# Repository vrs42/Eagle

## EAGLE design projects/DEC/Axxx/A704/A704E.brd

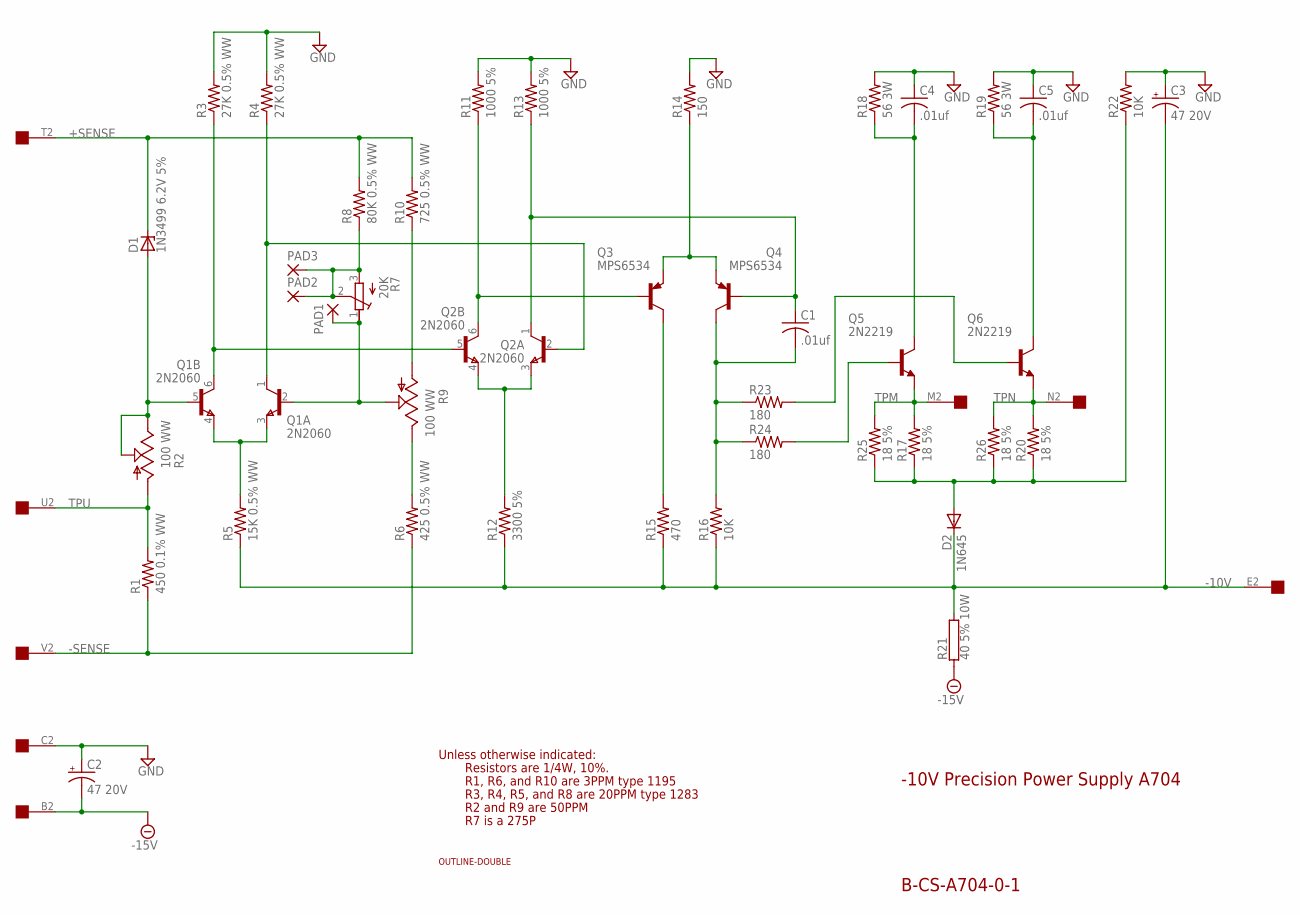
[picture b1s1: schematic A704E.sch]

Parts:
C1, C4, C5: .01uf; C050-025X075
C2, C3: 47 20V; E22-6
D1: 1N3499 6.2V 5%; DO35Z10
D2: 1N645; DO35-10
PAD1, PAD2, PAD3: 2,54/1,0
Q1, Q2: 2N2060; TO78
Q3, Q4: MPS6534; TO39
Q5, Q6: 2N2219; TO39
R1: 450 0.1% WW; P0817/22
R2, R9: 100 WW; S75P
R3, R4: 27K 0.5% WW; 0411/15
R5: 15K 0.5% WW; 0411/15
R6: 425 0.5% WW; P0817/22
R7: 20K; 3006Y
R8: 80K 0.5% WW; 0411/15
R10: 725 0.5% WW; P0817/22
R11, R13: 1000 5%; 0207/10
R12: 3300 5%; 0207/10
R14: 150; 0207/10
R15: 470; 0207/10
R16, R22: 10K; 0207/10
R17, R20, R25, R26: 18 5%; 0207/10
R18, R19: 56 3W; 0411/15
R21: 40 5% 10W; KH216-8
R23, R24: 180; 0207/10
U$2: OUTLINE-DOUBLE; DOUBLE
U$3: EDGE-1; EDGE-CON1

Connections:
+SENSE: D1.C, R8.2, R10.2, U$3.T2
-10V: C3.-, D2.C, R5.1, R12.1, R15.1, R16.1, R21.2, U$3.E2
-15V: C2.-, R21.1, U$3.B2
-SENSE: R1.1, R6.1, U$3.V2
GND: C2.+, C3.+, C4.1, C5.1, R3.2, R4.2, R11.2, R13.2, R14.2, R18.2, R19.2, R22.2, U$3.C2
unnamed: Q1.3 (E), Q1.4 (E), R5.2
unnamed: Q1.1 (C), Q2.2 (B), R4.1
unnamed: Q1.6 (C), Q2.5 (B), R3.1
unnamed: D1.A, Q1.5 (B), R2.E, R2.S
unnamed: R6.2, R9.E
unnamed: Q2.3 (E), Q2.4 (E), R12.2
unnamed: Q2.6 (C), Q3.2 (B), R11.1
unnamed: PAD1.1, Q1.2 (B), R7.1 (A), R9.S
unnamed: C1.1, Q2.1 (C), Q4.2 (B), R13.1
unnamed: Q3.3 (C), R15.2
unnamed: C1.2, Q4.3 (C), R16.2, R23.1, R24.1
unnamed: PAD2.1, PAD3.1, R7.2 (S), R7.3 (E), R8.1
unnamed: D2.A, R17.1, R20.1, R22.1, R25.1, R26.1
unnamed: Q3.1 (E), Q4.1 (E), R14.1
unnamed: Q5.2 (B), R24.2
unnamed: Q6.2 (B), R23.2
unnamed: C4.2, Q5.3 (C), R18.1
unnamed: C5.2, Q6.3 (C), R19.1
unnamed: R9.A, R10.1
TPM: Q5.1 (E), R17.2, R25.2, U$3.M2
TPN: Q6.1 (E), R20.2, R26.2, U$3.N2
TPU: R1.2, R2.A, U$3.U2

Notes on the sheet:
-10V Precision Power Supply A704
B-CS-A704-0-1
Unless otherwise indicated:
Resistors are 1/4W, 10%.
R7 is a 275P
R3, R4, R5, and R8 are 20PPM type 1283
R1, R6, and R10 are 3PPM type 1195
R2 and R9 are 50PPM

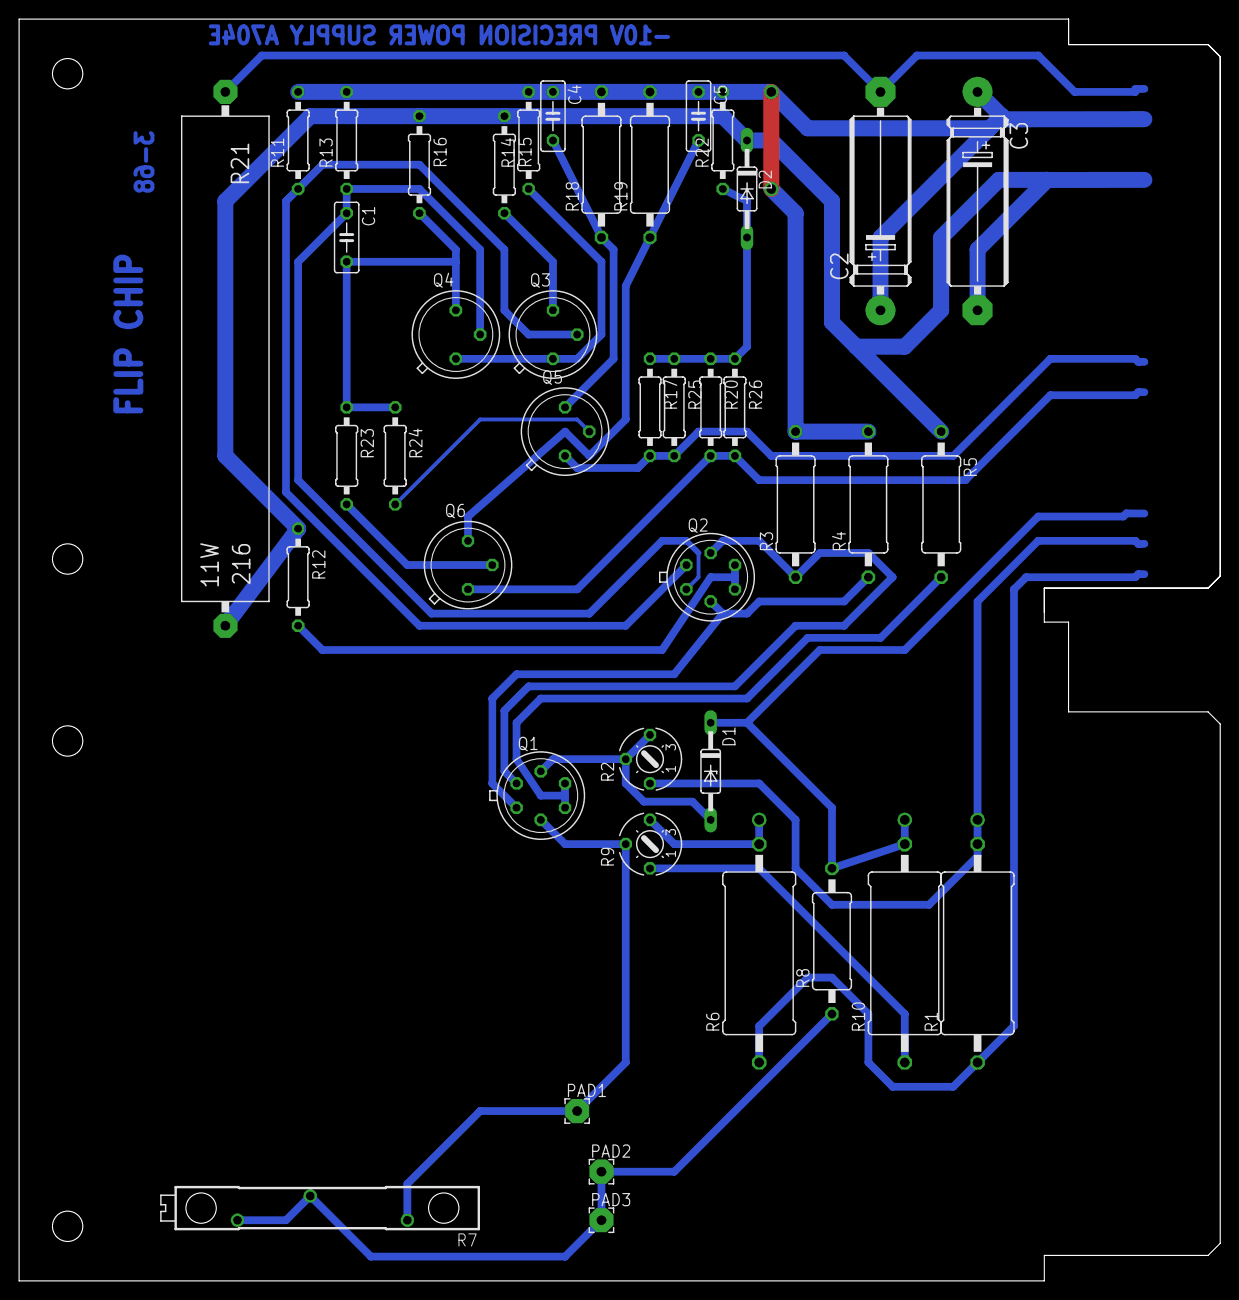
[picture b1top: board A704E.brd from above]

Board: 2 copper layers, 125.7 x 132.1 mm, 44 parts (0 on the bottom side), 27 nets.

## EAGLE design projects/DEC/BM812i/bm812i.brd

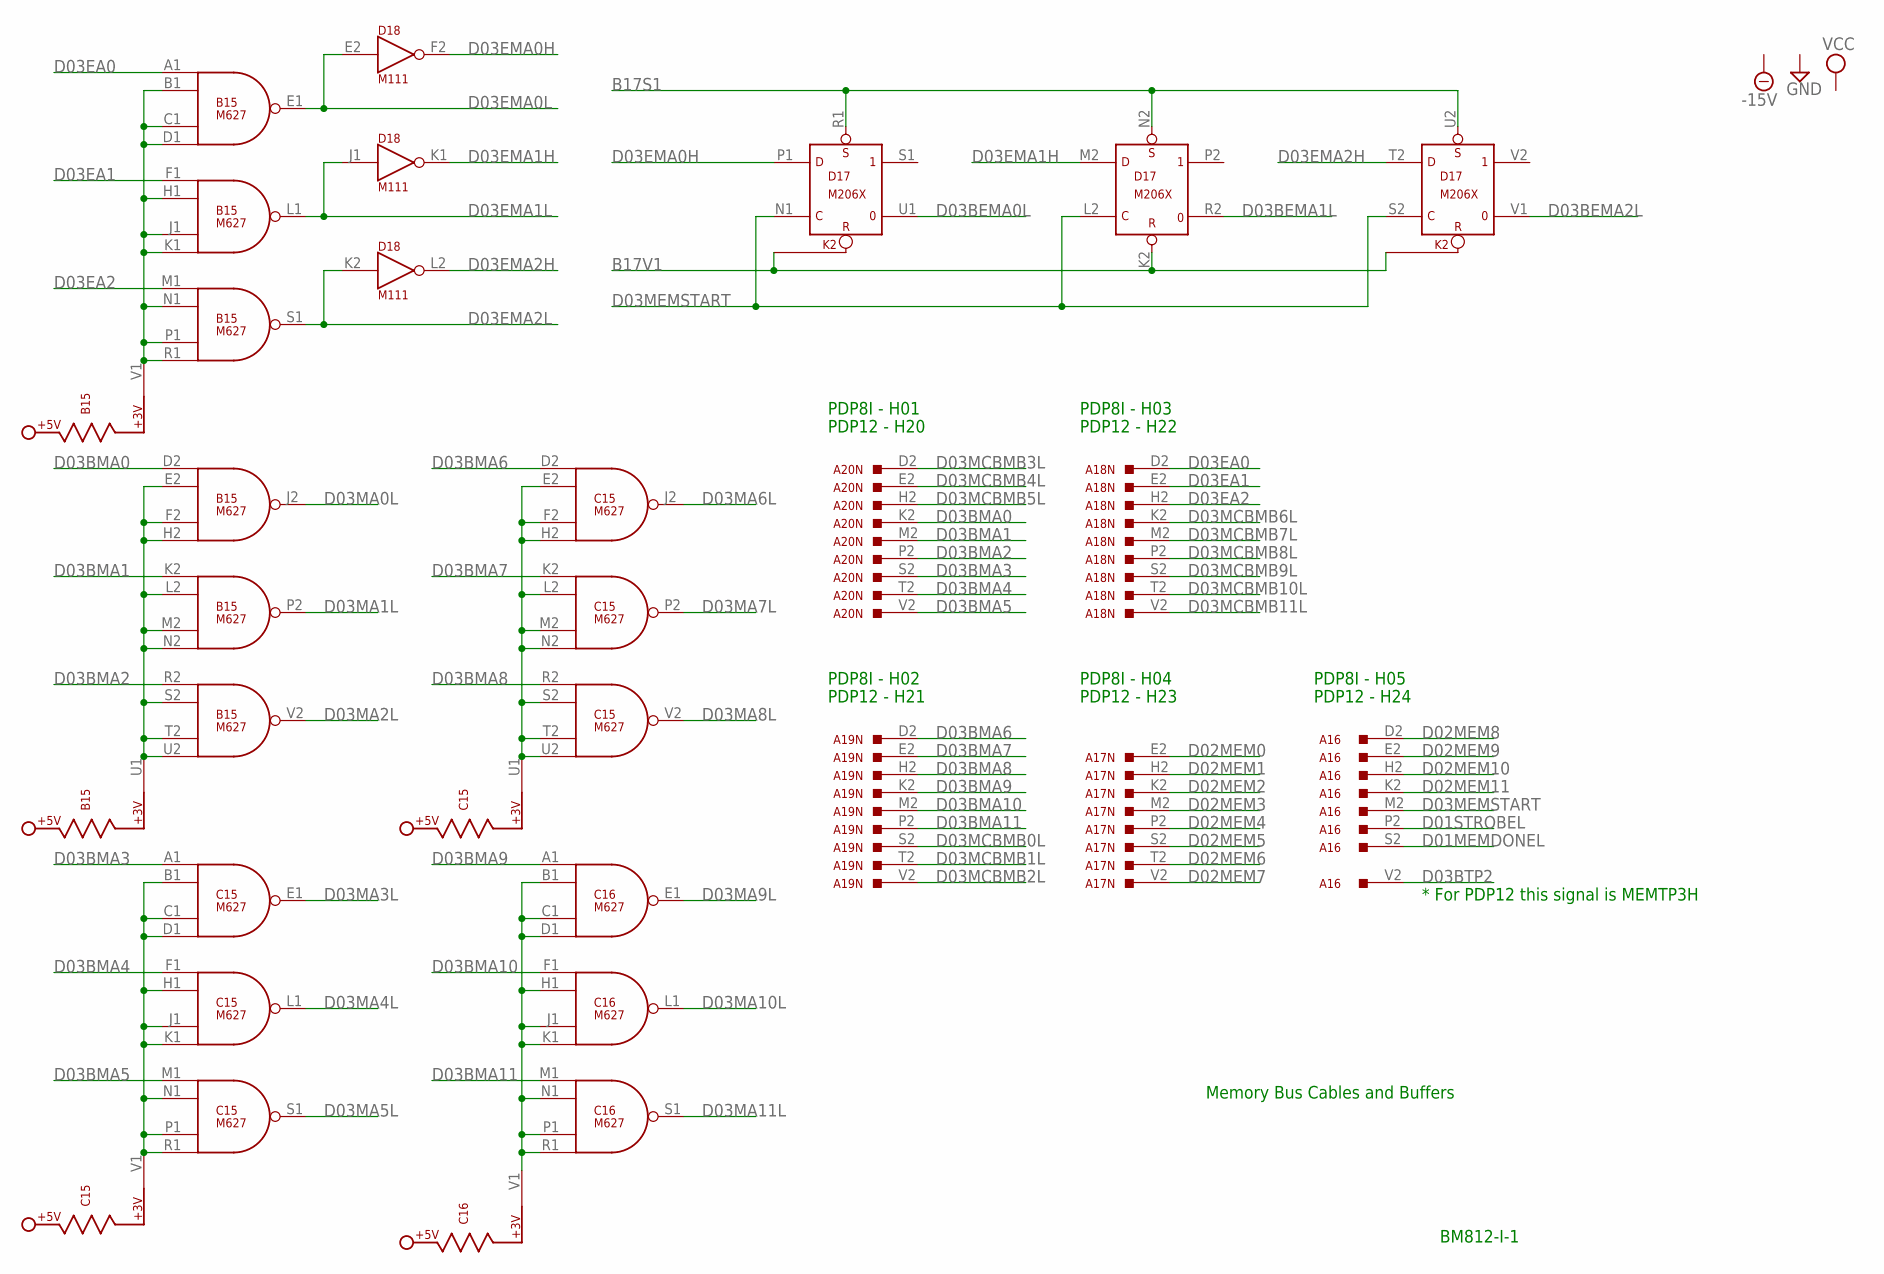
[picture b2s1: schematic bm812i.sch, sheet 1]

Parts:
A16, A17N, A18N, A19N, A20N: M903; H807
B15: M627; H807
C15, C16: M627; H807
D17: M206X; H807
D18: M111; H807

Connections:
B17S1: D17.N2 (S), D17.R1 (S), D17.U2 (S); also elsewhere on the board
B17V1: D17.K2 (R); also elsewhere on the board
D01MEMDONEL: A16.S2; also elsewhere on the board
D01STROBEL: A16.P2; also elsewhere on the board
D02MEM0: A17N.E2; also elsewhere on the board
D02MEM1: A17N.H2; also elsewhere on the board
D02MEM2: A17N.K2; also elsewhere on the board
D02MEM3: A17N.M2; also elsewhere on the board
D02MEM4: A17N.P2; also elsewhere on the board
D02MEM5: A17N.S2; also elsewhere on the board
D02MEM6: A17N.T2; also elsewhere on the board
D02MEM7: A17N.V2; also elsewhere on the board
D02MEM8: A16.D2; also elsewhere on the board
D02MEM9: A16.E2; also elsewhere on the board
D02MEM10: A16.H2; also elsewhere on the board
D02MEM11: A16.K2; also elsewhere on the board
D03BEMA0L: D17.U1 (0); also elsewhere on the board
D03BEMA1L: D17.R2 (0); also elsewhere on the board
D03BEMA2L: D17.V1 (0); also elsewhere on the board
D03BMA0: A20N.K2, B15.D2 (IN1)
D03BMA1: A20N.M2, B15.K2 (IN1)
D03BMA2: A20N.P2, B15.R2 (IN1)
D03BMA3: A20N.S2, C15.A1 (IN1)
D03BMA4: A20N.T2, C15.F1 (IN1)
D03BMA5: A20N.V2, C15.M1 (IN1)
D03BMA6: A19N.D2, C15.D2 (IN1)
D03BMA7: A19N.E2, C15.K2 (IN1)
D03BMA8: A19N.H2, C15.R2 (IN1)
D03BMA9: A19N.K2, C16.A1 (IN1)
D03BMA10: A19N.M2, C16.F1 (IN1)
D03BMA11: A19N.P2, C16.M1 (IN1)
D03BTP2: A16.V2; also elsewhere on the board
D03EA0: A18N.D2, B15.A1 (IN1)
D03EA1: A18N.E2, B15.F1 (IN1)
D03EA2: A18N.H2, B15.M1 (IN1)
D03EMA0H: D17.P1 (D), D18.F2 (OUT); also elsewhere on the board
D03EMA0L: B15.E1 (OUT), D18.E2 (IN); also elsewhere on the board
D03EMA1H: D17.M2 (D), D18.K1 (OUT); also elsewhere on the board
D03EMA1L: B15.L1 (OUT), D18.J1 (IN); also elsewhere on the board
D03EMA2H: D17.T2 (D), D18.L2 (OUT); also elsewhere on the board
D03EMA2L: B15.S1 (OUT), D18.K2 (IN); also elsewhere on the board
D03MA0L: B15.J2 (OUT); also elsewhere on the board
D03MA1L: B15.P2 (OUT); also elsewhere on the board
D03MA2L: B15.V2 (OUT); also elsewhere on the board
D03MA3L: C15.E1 (OUT); also elsewhere on the board
D03MA4L: C15.L1 (OUT); also elsewhere on the board
D03MA5L: C15.S1 (OUT); also elsewhere on the board
D03MA6L: C15.J2 (OUT); also elsewhere on the board
D03MA7L: C15.P2 (OUT); also elsewhere on the board
D03MA8L: C15.V2 (OUT); also elsewhere on the board
D03MA9L: C16.E1 (OUT); also elsewhere on the board
D03MA10L: C16.L1 (OUT); also elsewhere on the board
D03MA11L: C16.S1 (OUT); also elsewhere on the board
D03MCBMB0L: A19N.S2; also elsewhere on the board
D03MCBMB1L: A19N.T2; also elsewhere on the board
D03MCBMB2L: A19N.V2; also elsewhere on the board
D03MCBMB3L: A20N.D2; also elsewhere on the board
D03MCBMB4L: A20N.E2; also elsewhere on the board
D03MCBMB5L: A20N.H2; also elsewhere on the board
D03MCBMB6L: A18N.K2; also elsewhere on the board
D03MCBMB7L: A18N.M2; also elsewhere on the board
D03MCBMB8L: A18N.P2; also elsewhere on the board
D03MCBMB9L: A18N.S2; also elsewhere on the board
D03MCBMB10L: A18N.T2; also elsewhere on the board
D03MCBMB11L: A18N.V2; also elsewhere on the board
D03MEMSTART: A16.M2, D17.L2 (C), D17.N1 (C), D17.S2 (C); also elsewhere on the board
GND: A16.A1 (GND), A16.C1 (GND), A16.C2 (GND), A16.F1 (GND), A16.F2 (GND), A16.J2 (GND), A16.K1 (GND), A16.L2 (GND), A16.N1 (GND), A16.N2 (GND), A16.R1 (GND), A16.R2 (GND), A16.T1 (GND), A16.U2 (GND), A17N.A1 (GND), A17N.C1 (GND), A17N.C2 (GND), A17N.F1 (GND), A17N.F2 (GND), A17N.J2 (GND), A17N.K1 (GND), A17N.L2 (GND), A17N.N1 (GND), A17N.N2 (GND), A17N.R1 (GND), A17N.R2 (GND), A17N.T1 (GND), A17N.U2 (GND), A18N.A1 (GND), A18N.C1 (GND), A18N.C2 (GND), A18N.F1 (GND), A18N.F2 (GND), A18N.J2 (GND), A18N.K1 (GND), A18N.L2 (GND), A18N.N1 (GND), A18N.N2 (GND), A18N.R1 (GND), A18N.R2 (GND), A18N.T1 (GND), A18N.U2 (GND), A19N.A1 (GND), A19N.C1 (GND), A19N.C2 (GND), A19N.F1 (GND), A19N.F2 (GND), A19N.J2 (GND), A19N.K1 (GND), A19N.L2 (GND), A19N.N1 (GND), A19N.N2 (GND), A19N.R1 (GND), A19N.R2 (GND), A19N.T1 (GND), A19N.U2 (GND), A20N.A1 (GND), A20N.C1 (GND), A20N.C2 (GND), A20N.F1 (GND), A20N.F2 (GND), A20N.J2 (GND), A20N.K1 (GND), A20N.L2 (GND), A20N.N1 (GND), A20N.N2 (GND), A20N.R1 (GND), A20N.R2 (GND), A20N.T1 (GND), A20N.U2 (GND), B15.C2 (GND), B15.T1 (GND), C15.C2 (GND), C15.T1 (GND), C16.C2 (GND), C16.T1 (GND), D17.C2 (GND), D17.T1 (GND), D18.C2 (GND), D18.T1 (GND); also elsewhere on the board
unnamed: B15.B1 (IN2), B15.C1 (IN3), B15.D1 (IN4), B15.H1 (IN2), B15.J1 (IN3), B15.K1 (IN4), B15.N1 (IN2), B15.P1 (IN3), B15.R1 (IN4), B15.V1
unnamed: B15.E2 (IN2), B15.F2 (IN3), B15.H2 (IN4), B15.L2 (IN2), B15.M2 (IN3), B15.N2 (IN4), B15.S2 (IN2), B15.T2 (IN3), B15.U1, B15.U2 (IN4)
unnamed: C15.B1 (IN2), C15.C1 (IN3), C15.D1 (IN4), C15.H1 (IN2), C15.J1 (IN3), C15.K1 (IN4), C15.N1 (IN2), C15.P1 (IN3), C15.R1 (IN4), C15.V1
unnamed: C15.E2 (IN2), C15.F2 (IN3), C15.H2 (IN4), C15.L2 (IN2), C15.M2 (IN3), C15.N2 (IN4), C15.S2 (IN2), C15.T2 (IN3), C15.U1, C15.U2 (IN4)
unnamed: C16.B1 (IN2), C16.C1 (IN3), C16.D1 (IN4), C16.H1 (IN2), C16.J1 (IN3), C16.K1 (IN4), C16.N1 (IN2), C16.P1 (IN3), C16.R1 (IN4), C16.V1
VCC: B15.A2 (VCC), C15.A2 (VCC), C16.A2 (VCC), D17.A2 (VCC), D18.A2 (VCC); also elsewhere on the board

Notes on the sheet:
Memory Bus Cables and Buffers
BM812-I-1
* For PDP12 this signal is MEMTP3H
PDP8I - H01
PDP8I - H02
PDP8I - H03
PDP8I - H04
PDP8I - H05
PDP12 - H20
PDP12 - H21
PDP12 - H22
PDP12 - H23
PDP12 - H24

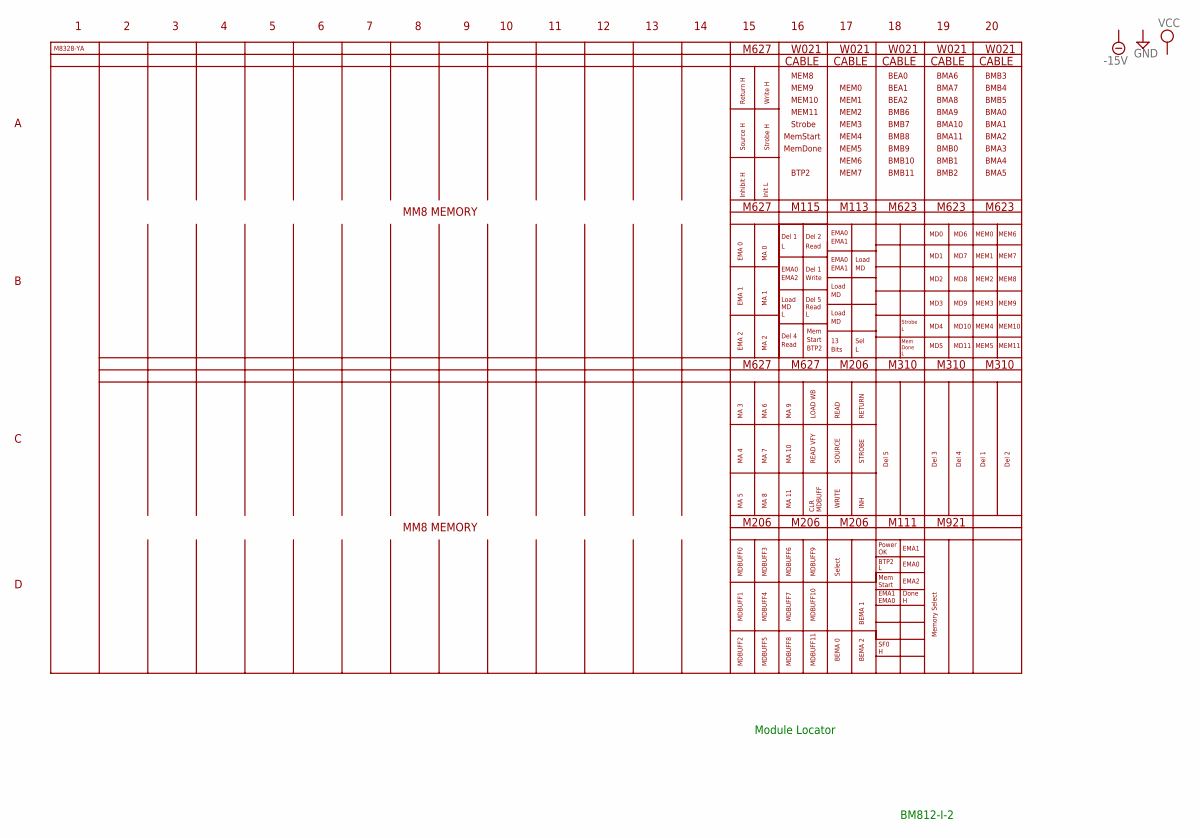
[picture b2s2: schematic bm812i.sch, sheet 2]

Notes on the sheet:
Module Locator
BM812-I-2
M8328-YA
MM8 MEMORY
M627
W021
M115
M113
M623
M206
M111
M921
M310
CABLE
Source H
Strobe H
Return H
Write H
Init L
Inhibit H
Select
BEMA 0
BEMA 1
BEMA 2
Del 1
Del 2
Del 3
Del 4
Del 5
Memory Select
Power
BTP2
Mem
Start
EMA1
EMA0
SF0
Done
EMA2
MDBUFF0

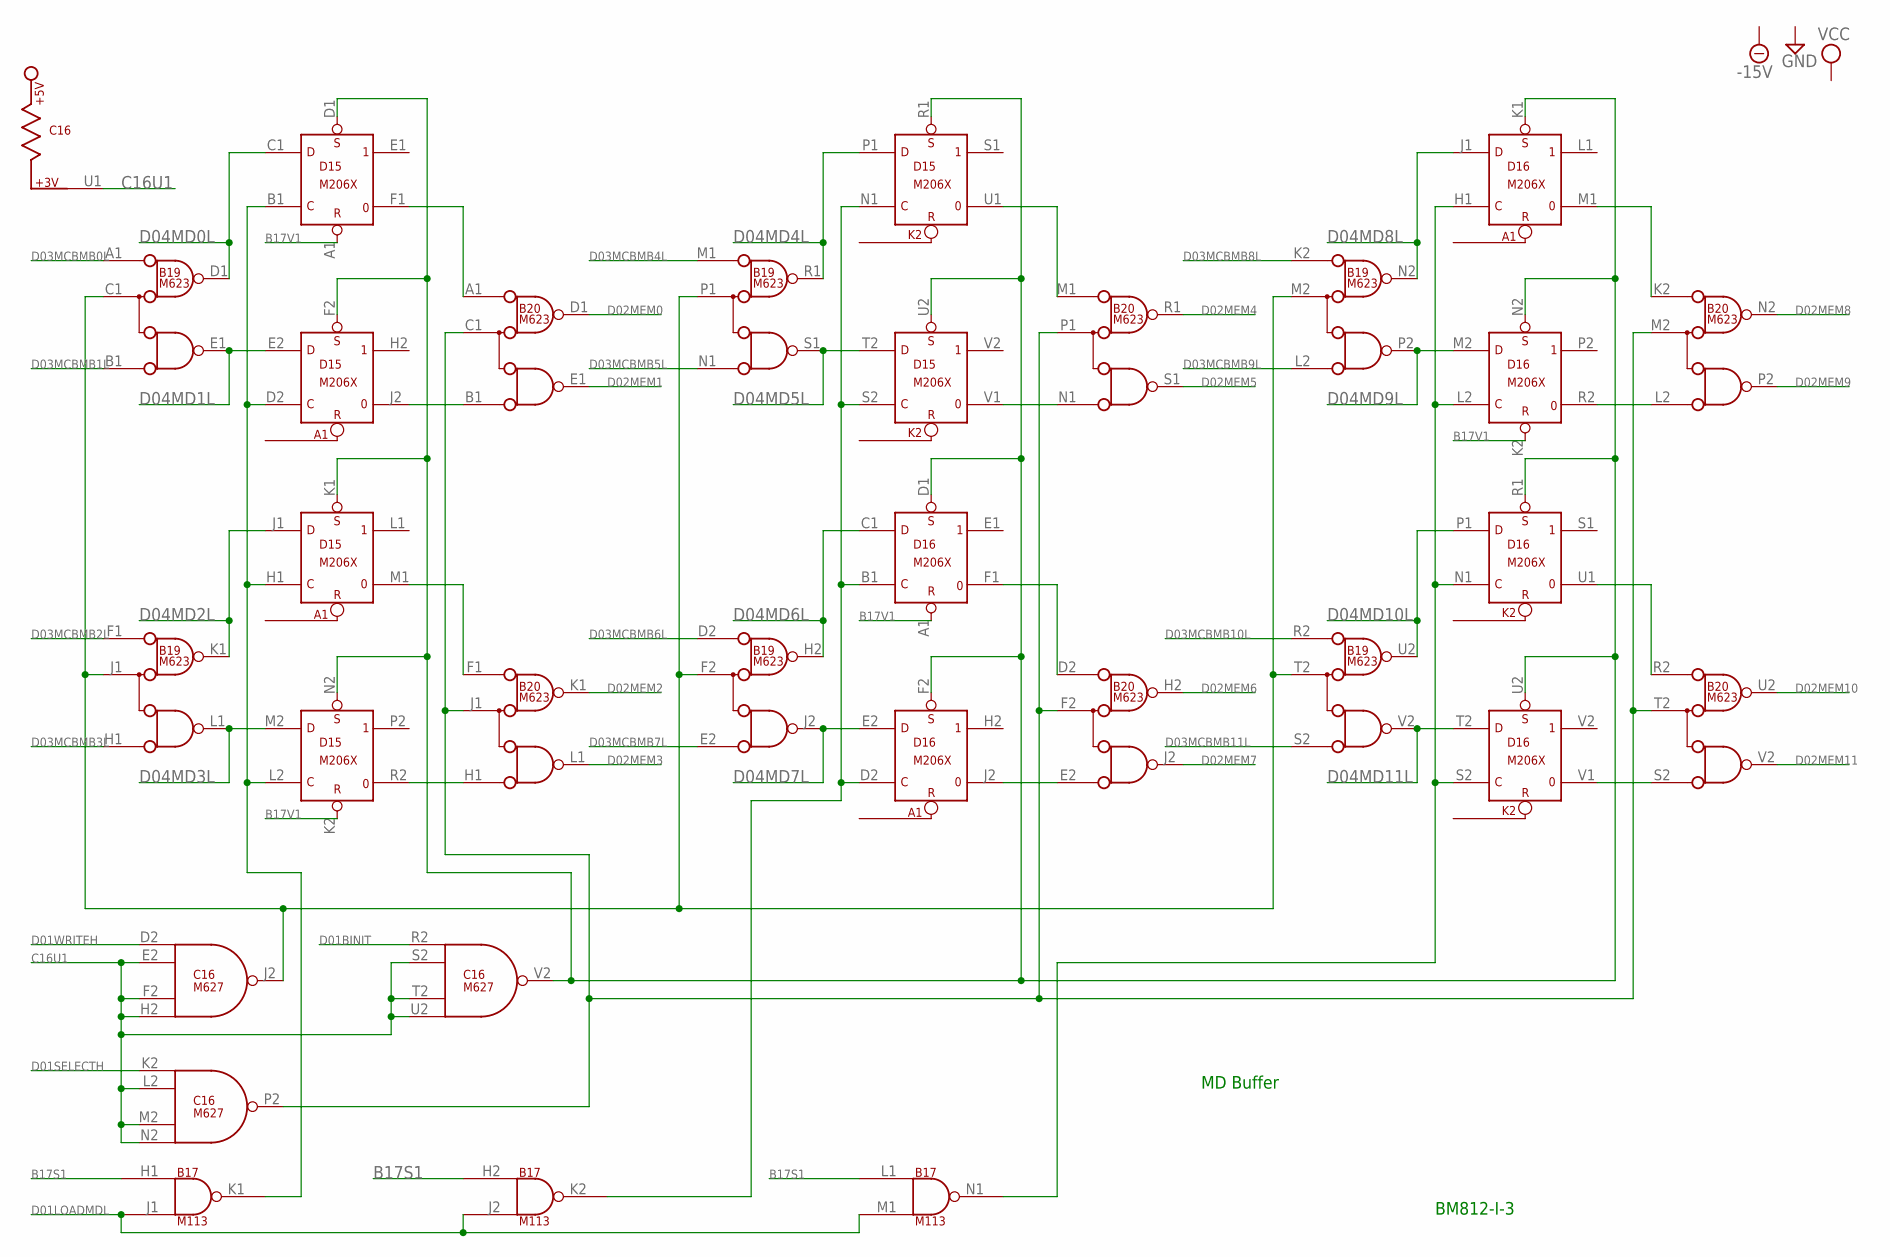
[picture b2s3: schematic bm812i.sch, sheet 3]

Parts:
B17: M113; H807
B19, B20: M623; H807
C16: M627; H807
D15, D16: M206X; H807

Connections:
B17S1: B17.H1 (IN1), B17.H2 (IN1), B17.L1 (IN1); also elsewhere on the board
B17V1: D15.A1 (R), D15.K2 (R), D16.A1 (R), D16.K2 (R); also elsewhere on the board
C16U1: C16.E2 (IN2), C16.F2 (IN3), C16.H2 (IN4), C16.L2 (IN2), C16.M2 (IN3), C16.N2 (IN4), C16.S2 (IN2), C16.T2 (IN3), C16.U1, C16.U2 (IN4)
D01BINIT: C16.R2 (IN1); also elsewhere on the board
D01LOADMDL: B17.J1 (IN2), B17.J2 (IN2), B17.M1 (IN2); also elsewhere on the board
D01SELECTH: C16.K2 (IN1); also elsewhere on the board
D01WRITEH: C16.D2 (IN1); also elsewhere on the board
D02MEM0: B20.D1 (D); also elsewhere on the board
D02MEM1: B20.E1 (E); also elsewhere on the board
D02MEM2: B20.K1 (D); also elsewhere on the board
D02MEM3: B20.L1 (E); also elsewhere on the board
D02MEM4: B20.R1 (D); also elsewhere on the board
D02MEM5: B20.S1 (E); also elsewhere on the board
D02MEM6: B20.H2 (D); also elsewhere on the board
D02MEM7: B20.J2 (E); also elsewhere on the board
D02MEM8: B20.N2 (D); also elsewhere on the board
D02MEM9: B20.P2 (E); also elsewhere on the board
D02MEM10: B20.U2 (D); also elsewhere on the board
D02MEM11: B20.V2 (E); also elsewhere on the board
D03MCBMB0L: B19.A1 (A); also elsewhere on the board
D03MCBMB1L: B19.B1 (B); also elsewhere on the board
D03MCBMB2L: B19.F1 (A); also elsewhere on the board
D03MCBMB3L: B19.H1 (B); also elsewhere on the board
D03MCBMB4L: B19.M1 (A); also elsewhere on the board
D03MCBMB5L: B19.N1 (B); also elsewhere on the board
D03MCBMB6L: B19.D2 (A); also elsewhere on the board
D03MCBMB7L: B19.E2 (B); also elsewhere on the board
D03MCBMB8L: B19.K2 (A); also elsewhere on the board
D03MCBMB9L: B19.L2 (B); also elsewhere on the board
D03MCBMB10L: B19.R2 (A); also elsewhere on the board
D03MCBMB11L: B19.S2 (B); also elsewhere on the board
D04MD0L: B19.D1 (D), D15.C1 (D); also elsewhere on the board
D04MD1L: B19.E1 (E), D15.E2 (D); also elsewhere on the board
D04MD2L: B19.K1 (D), D15.J1 (D); also elsewhere on the board
D04MD3L: B19.L1 (E), D15.M2 (D); also elsewhere on the board
D04MD4L: B19.R1 (D), D15.P1 (D); also elsewhere on the board
D04MD5L: B19.S1 (E), D15.T2 (D); also elsewhere on the board
D04MD6L: B19.H2 (D), D16.C1 (D); also elsewhere on the board
D04MD7L: B19.J2 (E), D16.E2 (D); also elsewhere on the board
D04MD8L: B19.N2 (D), D16.J1 (D); also elsewhere on the board
D04MD9L: B19.P2 (E), D16.M2 (D); also elsewhere on the board
D04MD10L: B19.U2 (D), D16.P1 (D); also elsewhere on the board
D04MD11L: B19.V2 (E), D16.T2 (D); also elsewhere on the board
GND: B17.C2 (GND), B17.T1 (GND), B19.C2 (GND), B19.T1 (GND), B19.U1 (GND), B19.V1 (GND), B20.C2 (GND), B20.T1 (GND), B20.U1 (GND), B20.V1 (GND), C16.C2 (GND), C16.T1 (GND), D15.C2 (GND), D15.T1 (GND), D16.C2 (GND), D16.T1 (GND); also elsewhere on the board
unnamed: B17.K1 (OUT), D15.B1 (C), D15.D2 (C), D15.H1 (C), D15.L2 (C)
unnamed: B20.H1 (B), D15.R2 (0)
unnamed: B20.A1 (A), D15.F1 (0)
unnamed: B20.B1 (B), D15.J2 (0)
unnamed: B17.K2 (OUT), D15.N1 (C), D15.S2 (C), D16.B1 (C), D16.D2 (C)
unnamed: B20.F1 (A), D15.M1 (0)
unnamed: B19.C1 (C), B19.F2 (C), B19.J1 (C), B19.M2 (C), B19.P1 (C), B19.T2 (C), C16.J2 (OUT)
unnamed: C16.V2 (OUT), D15.D1 (S), D15.F2 (S), D15.K1 (S), D15.N2 (S), D15.R1 (S), D15.U2 (S), D16.D1 (S), D16.F2 (S), D16.K1 (S), D16.N2 (S), D16.R1 (S), D16.U2 (S)
unnamed: B20.C1 (C), B20.F2 (C), B20.J1 (C), B20.M2 (C), B20.P1 (C), B20.T2 (C), C16.P2 (OUT)
unnamed: B20.N1 (B), D15.V1 (0)
unnamed: B20.E2 (B), D16.J2 (0)
unnamed: B20.D2 (A), D16.F1 (0)
unnamed: B20.M1 (A), D15.U1 (0)
unnamed: B20.S2 (B), D16.V1 (0)
unnamed: B20.R2 (A), D16.U1 (0)
unnamed: B17.N1 (OUT), D16.H1 (C), D16.L2 (C), D16.N1 (C), D16.S2 (C)
unnamed: B20.L2 (B), D16.R2 (0)
unnamed: B20.K2 (A), D16.M1 (0)
VCC: B17.A2 (VCC), B19.A2 (VCC), B20.A2 (VCC), C16.A2 (VCC), D15.A2 (VCC), D16.A2 (VCC); also elsewhere on the board

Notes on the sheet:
MD Buffer
BM812-I-3

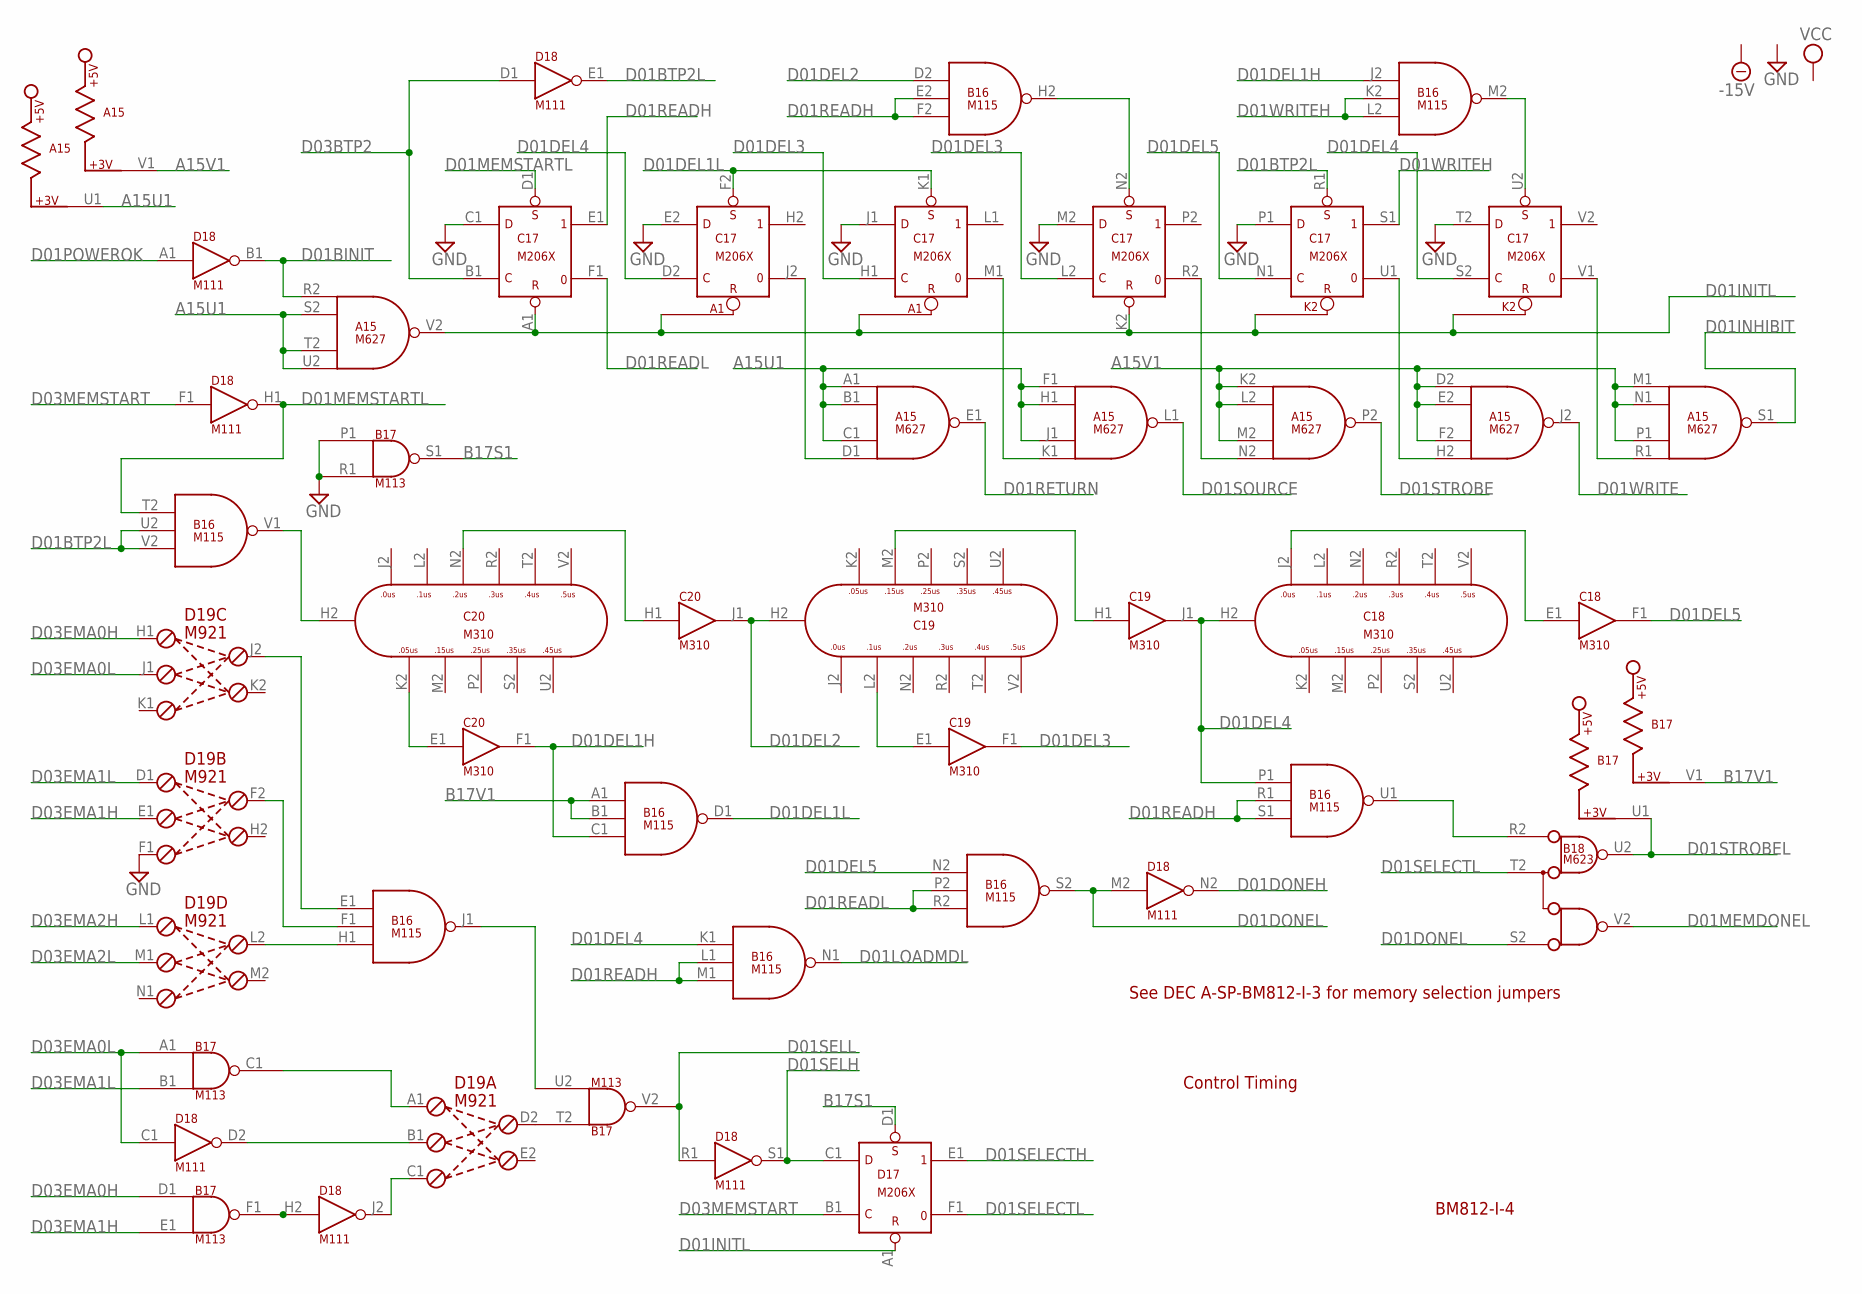
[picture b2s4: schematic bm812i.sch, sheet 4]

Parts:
A15: M627; H807
B16: M115; H807
B17: M113; H807
B18: M623; H807
C17: M206X; H807
C18, C19, C20: M310; H807
D17: M206X; H807
D18: M111; H807
D19: M921; H807

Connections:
A15U1: A15.A1 (IN1), A15.B1 (IN2), A15.C1 (IN3), A15.F1 (IN1), A15.H1 (IN2), A15.J1 (IN3), A15.S2 (IN2), A15.T2 (IN3), A15.U1, A15.U2 (IN4); also elsewhere on the board
A15V1: A15.D2 (IN1), A15.E2 (IN2), A15.F2 (IN3), A15.K2 (IN1), A15.L2 (IN2), A15.M1 (IN1), A15.M2 (IN3), A15.N1 (IN2), A15.P1 (IN3), A15.V1
B17S1: B17.S1 (OUT), D17.D1 (S); also elsewhere on the board
B17V1: B16.A1 (IN1), B16.B1 (IN2), B17.V1; also elsewhere on the board
D01BINIT: A15.R2 (IN1), D18.B1 (OUT); also elsewhere on the board
D01BTP2L: B16.U2 (IN2), B16.V2 (IN3), C17.R1 (S), D18.E1 (OUT)
D01DEL1H: B16.C1 (IN3), B16.J2 (IN1), C20.F1 (OUT)
D01DEL1L: B16.D1 (OUT), C17.F2 (S), C17.K1 (S)
D01DEL2: B16.D2 (IN1), C19.H2, C20.J1 (OUT)
D01DEL3: C17.H1 (C), C17.L2 (C), C19.F1 (OUT)
D01DEL4: B16.K1 (IN1), B16.P1 (IN1), C17.D2 (C), C17.S2 (C), C18.H2, C19.J1 (OUT)
D01DEL5: B16.N2 (IN1), C17.N1 (C), C18.F1 (OUT)
D01DONEH: D18.N2 (OUT); also elsewhere on the board
D01DONEL: B16.S2 (OUT), B18.S2 (B), D18.M2 (IN)
D01INHIBIT: A15.S1 (OUT); also elsewhere on the board
D01INITL: A15.V2 (OUT), C17.A1 (R), C17.K2 (R), D17.A1 (R)
D01LOADMDL: B16.N1 (OUT); also elsewhere on the board
D01MEMDONEL: B18.V2 (E); also elsewhere on the board
D01MEMSTARTL: B16.T2 (IN1), C17.D1 (S), D18.H1 (OUT)
D01POWEROK: D18.A1 (IN); also elsewhere on the board
D01READH: B16.E2 (IN2), B16.F2 (IN3), B16.L1 (IN2), B16.M1 (IN3), B16.R1 (IN2), B16.S1 (IN3), C17.E1 (1)
D01READL: B16.P2 (IN2), B16.R2 (IN3), C17.F1 (0); also elsewhere on the board
D01RETURN: A15.E1 (OUT); also elsewhere on the board
D01SELECTH: D17.E1 (1); also elsewhere on the board
D01SELECTL: B18.T2 (C), D17.F1 (0)
D01SELH: D17.C1 (D), D18.S1 (OUT)
D01SELL: B17.V2 (OUT), D18.R1 (IN)
D01SOURCE: A15.L1 (OUT); also elsewhere on the board
D01STROBE: A15.P2 (OUT); also elsewhere on the board
D01STROBEL: B17.U1, B18.U2 (D); also elsewhere on the board
D01WRITE: A15.J2 (OUT); also elsewhere on the board
D01WRITEH: B16.K2 (IN2), B16.L2 (IN3), C17.S1 (1); also elsewhere on the board
D03BTP2: C17.B1 (C), D18.D1 (IN); also elsewhere on the board
D03EMA0H: B17.D1 (IN1), D19.H1 (L1); also elsewhere on the board
D03EMA0L: B17.A1 (IN1), D18.C1 (IN), D19.J1 (L2); also elsewhere on the board
D03EMA1H: B17.E1 (IN2), D19.E1 (L2); also elsewhere on the board
D03EMA1L: B17.B1 (IN2), D19.D1 (L1); also elsewhere on the board
D03EMA2H: D19.L1; also elsewhere on the board
D03EMA2L: D19.M1 (L2); also elsewhere on the board
D03MEMSTART: D17.B1 (C), D18.F1 (IN); also elsewhere on the board
GND: A15.C2 (GND), A15.T1 (GND), B16.C2 (GND), B16.T1 (GND), B17.C2 (GND), B17.P1 (IN1), B17.R1 (IN2), B17.T1 (GND), B18.C2 (GND), B18.T1 (GND), B18.U1 (GND), B18.V1 (GND), C17.C1 (D), C17.C2 (GND), C17.E2 (D), C17.J1 (D), C17.M2 (D), C17.P1 (D), C17.T1 (GND), C17.T2 (D), C18.C2 (GND), C18.T1 (GND), C19.C2 (GND), C19.T1 (GND), C20.C2 (GND), C20.T1 (GND), D17.C2 (GND), D17.T1 (GND), D18.C2 (GND), D18.T1 (GND), D19.F1 (L3); also elsewhere on the board
unnamed: C19.H1 (IN), C19.M2
unnamed: B16.V1 (OUT), C20.H2
unnamed: B16.H2 (OUT), C17.N2 (S)
unnamed: B17.C1 (OUT), D19.A1 (L1)
unnamed: C20.E1 (IN), C20.K2
unnamed: B16.M2 (OUT), C17.U2 (S)
unnamed: C20.H1 (IN), C20.N2
unnamed: B16.U1 (OUT), B18.R2 (A)
unnamed: A15.D1 (IN4), C17.J2 (0)
unnamed: C19.E1 (IN), C19.L2
unnamed: C18.E1 (IN), C18.J2
unnamed: A15.K1 (IN4), C17.M1 (0)
unnamed: A15.N2 (IN4), C17.R2 (0)
unnamed: D18.D2 (OUT), D19.B1 (L2)
unnamed: A15.H2 (IN4), C17.U1 (0)
unnamed: B17.F1 (OUT), D18.H2 (IN)
unnamed: A15.R1 (IN4), C17.V1 (0)
unnamed: D18.J2 (OUT), D19.C1 (L3)
unnamed: B17.T2 (IN1), D19.D2 (R1)
unnamed: B16.H1 (IN3), D19.L2 (R1)
unnamed: B16.F1 (IN2), D19.F2 (R1)
unnamed: B16.E1 (IN1), D19.J2 (R1)
unnamed: B16.J1 (OUT), B17.U2 (IN2)
VCC: A15.A2 (VCC), B16.A2 (VCC), B17.A2 (VCC), B18.A2 (VCC), C17.A2 (VCC), C18.A2 (VCC), C19.A2 (VCC), C20.A2 (VCC), D17.A2 (VCC), D18.A2 (VCC); also elsewhere on the board

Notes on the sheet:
BM812-I-4
Control Timing
See DEC A-SP-BM812-I-3 for memory selection jumpers
